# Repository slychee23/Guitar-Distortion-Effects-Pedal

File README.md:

# guitar-distortion-effects-pedal
This is JUJUBE--a custom analog guitar distortion effects pedal using the RC4558 dual op-amp.
<br>
Includes CAD of enclosure with labeled knob controls, optimizing component layouts
<br>
The circuit features:  
<br>
-Three potentiometers for user-adjustable gain, tone, and volume control  
<br>
-A 3PDT footswitch for true bypass switching, with integrated LED indicators for visual feedback  
<br>
-Two 1N4148 silicon diodes configured for symmetrical clipping, creating a distinct, aggressive distortion tone  
<br>

<p align="center">

## Schematic
<p align="center">

## Enclosure
<p align="center">

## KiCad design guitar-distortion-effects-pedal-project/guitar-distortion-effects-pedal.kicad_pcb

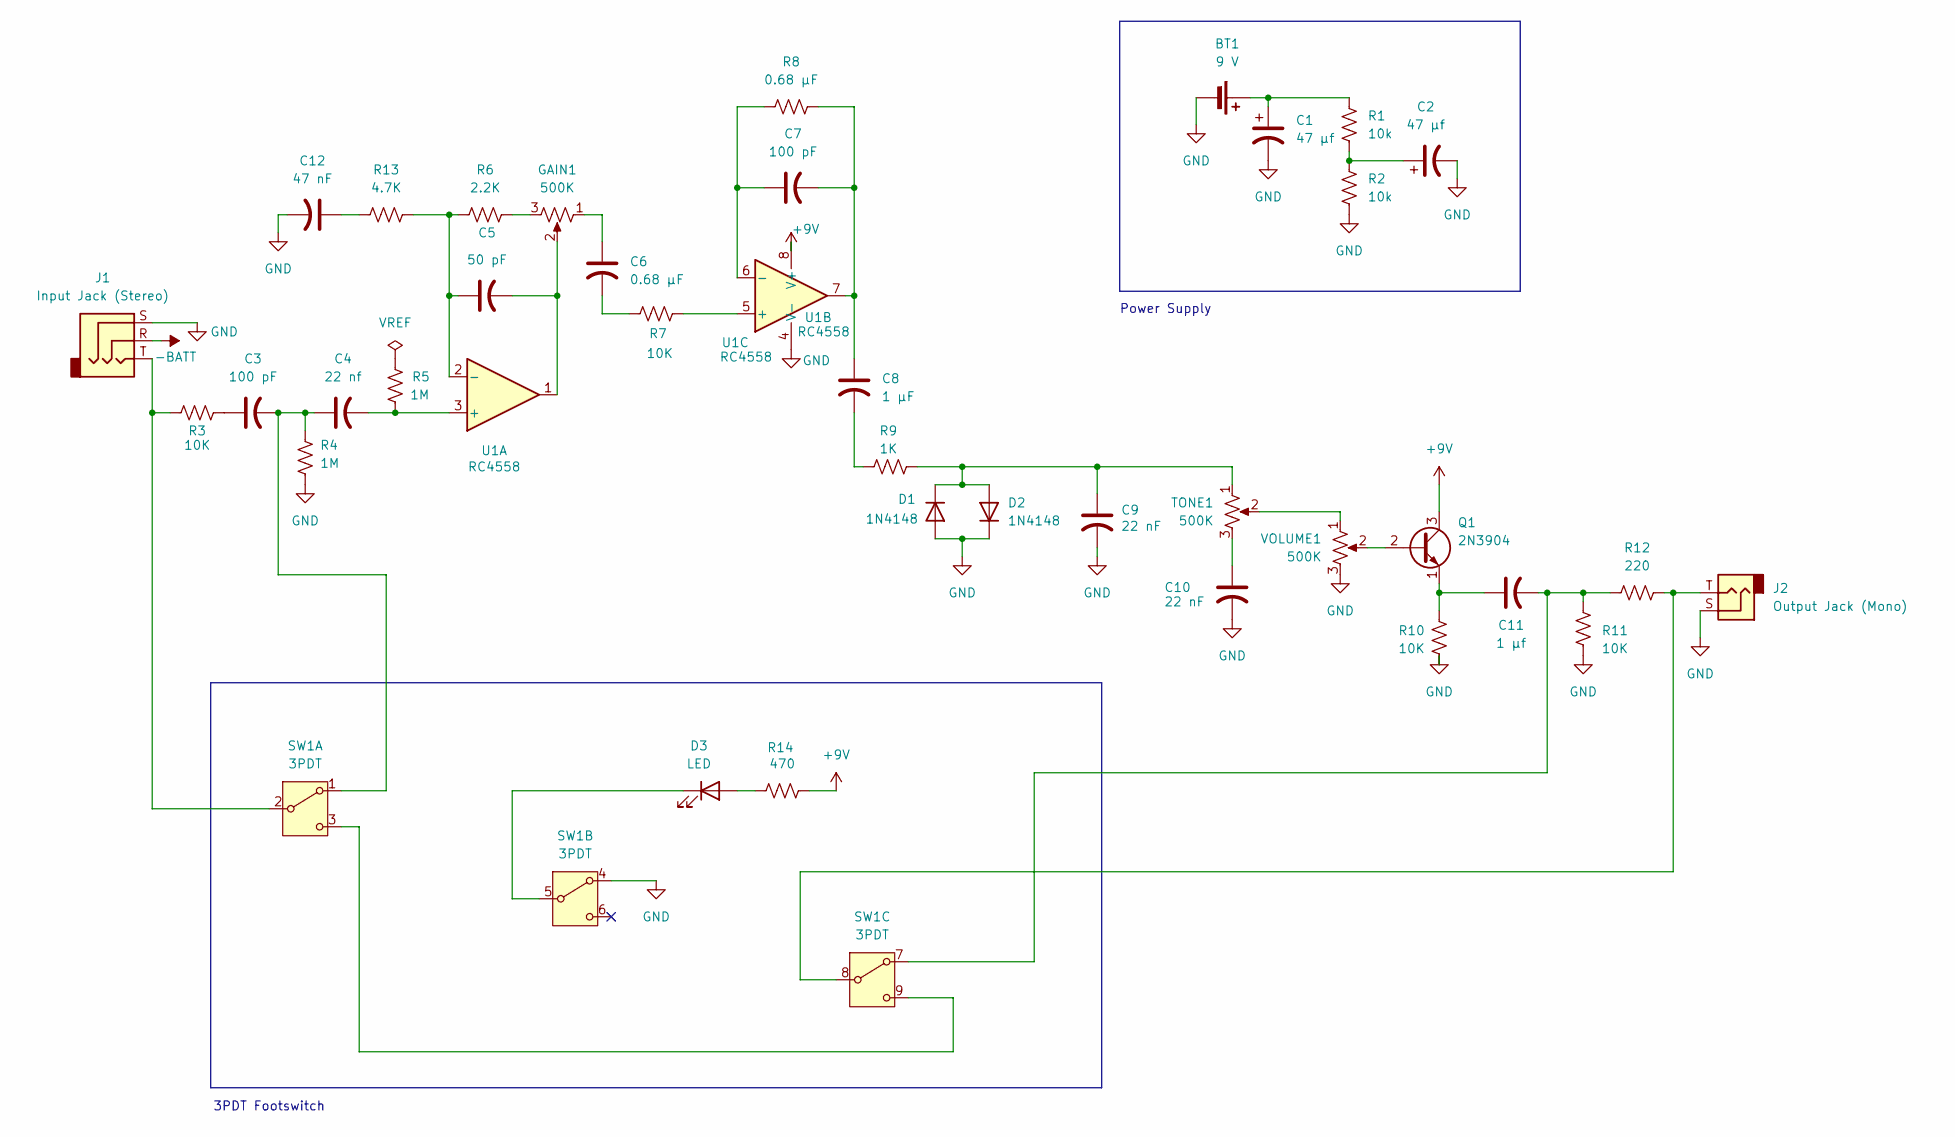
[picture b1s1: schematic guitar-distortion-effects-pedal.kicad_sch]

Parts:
BT1: 9 V; PinSocket_1x02_P2.54mm_Vertical
C1, C2: 47 μf; CP_Radial_D5.0mm_P2.00mm
C3, C7: 100 pF; C_Disc_D4.3mm_W1.9mm_P5.00mm
C4: 22 nf; C_Disc_D4.3mm_W1.9mm_P5.00mm
C5: 50 pF; C_Disc_D4.3mm_W1.9mm_P5.00mm
C6: 0.68 μF; C_Disc_D4.3mm_W1.9mm_P5.00mm
C8: 1 μF; C_Disc_D4.3mm_W1.9mm_P5.00mm
C9, C10: 22 nF; C_Disc_D4.3mm_W1.9mm_P5.00mm
C11: 1 μf; C_Disc_D4.3mm_W1.9mm_P5.00mm
C12: 47 nF; C_Disc_D4.3mm_W1.9mm_P5.00mm
D1, D2: 1N4148; D_DO-41_SOD81_P7.62mm_Horizontal
D3: LED; LED_D5.0mm
GAIN1: 500K; Potentiometer_Bourns_3386W_Horizontal
J1: Input Jack (Stereo); Jack_6.35mm_Neutrik_NJ3FD-V_Vertical
J2: Output Jack (Mono); Jack_6.35mm_Neutrik_NJ2FD-V_Vertical
Q1: 2N3904; TO-92_Inline
R1, R2: 10k; R_Axial_DIN0207_L6.3mm_D2.5mm_P7.62mm_Horizontal
R3, R7, R10, R11: 10K; R_Axial_DIN0207_L6.3mm_D2.5mm_P7.62mm_Horizontal
R4, R5: 1M; R_Axial_DIN0207_L6.3mm_D2.5mm_P7.62mm_Horizontal
R6: 2.2K; R_Axial_DIN0207_L6.3mm_D2.5mm_P7.62mm_Horizontal
R8: 0.68 μF; R_Axial_DIN0207_L6.3mm_D2.5mm_P7.62mm_Horizontal
R9: 1K; R_Axial_DIN0207_L6.3mm_D2.5mm_P7.62mm_Horizontal
R12: 220; R_Axial_DIN0207_L6.3mm_D2.5mm_P7.62mm_Horizontal
R13: 4.7K; R_Axial_DIN0207_L6.3mm_D2.5mm_P7.62mm_Horizontal
R14: 470; R_Axial_DIN0207_L6.3mm_D2.5mm_P7.62mm_Horizontal
SW1: 3PDT; 3PDT_Footswitch
TONE1: 500K; Potentiometer_Bourns_3386W_Horizontal
U1: RC4558; SOIC-8_3.9x4.9mm_P1.27mm
VOLUME1: 500K; Potentiometer_Bourns_3386W_Horizontal

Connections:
+9V: Q1.3 (C), R14.2, U1.8 (V+)
-BATT: J1.R
GND: BT1.2 (-), C1.2, C2.2, C9.2, C10.2, C12.2, D1.2 (A), D2.1 (K), J1.S, J2.S, R2.2, R4.2, R10.2, R11.2, SW1.4 (A), U1.4 (V-), VOLUME1.3
unnamed: BT1.1 (+), C1.1, R1.1
unnamed: C2.1, R1.2, R2.1
unnamed: C3.1, R3.2
unnamed: C5.2, GAIN1.2, U1.1
unnamed: C6.1, GAIN1.1
unnamed: C6.2, R7.1
unnamed: C7.2, C8.1, R8.2, U1.7
unnamed: C8.2, R9.1
unnamed: C10.1, TONE1.3
unnamed: C12.1, R13.1
unnamed: C9.1, D1.1 (K), D2.2 (A), R9.2, TONE1.1
unnamed: D3.2 (A), R14.1
unnamed: D3.1 (K), SW1.5 (B)
unnamed: GAIN1.3, R6.2
unnamed: Q1.2 (B), VOLUME1.2
unnamed: C11.1, Q1.1 (E), R10.1
unnamed: C3.2, C4.1, R4.1, SW1.1 (A)
unnamed: J1.T, R3.1, SW1.2 (B)
unnamed: SW1.3 (C), SW1.9 (C)
unnamed: C11.2, R11.1, R12.1, SW1.7 (A)
unnamed: J2.T, R12.2, SW1.8 (B)
unnamed: TONE1.2, VOLUME1.1
unnamed: C4.2, R5.2, U1.3 (+)
unnamed: C5.1, R6.1, R13.2, U1.2 (-)
unnamed: R7.2, U1.5 (+)
unnamed: C7.1, R8.1, U1.6 (-)

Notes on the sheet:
Power Supply
3PDT Footswitch

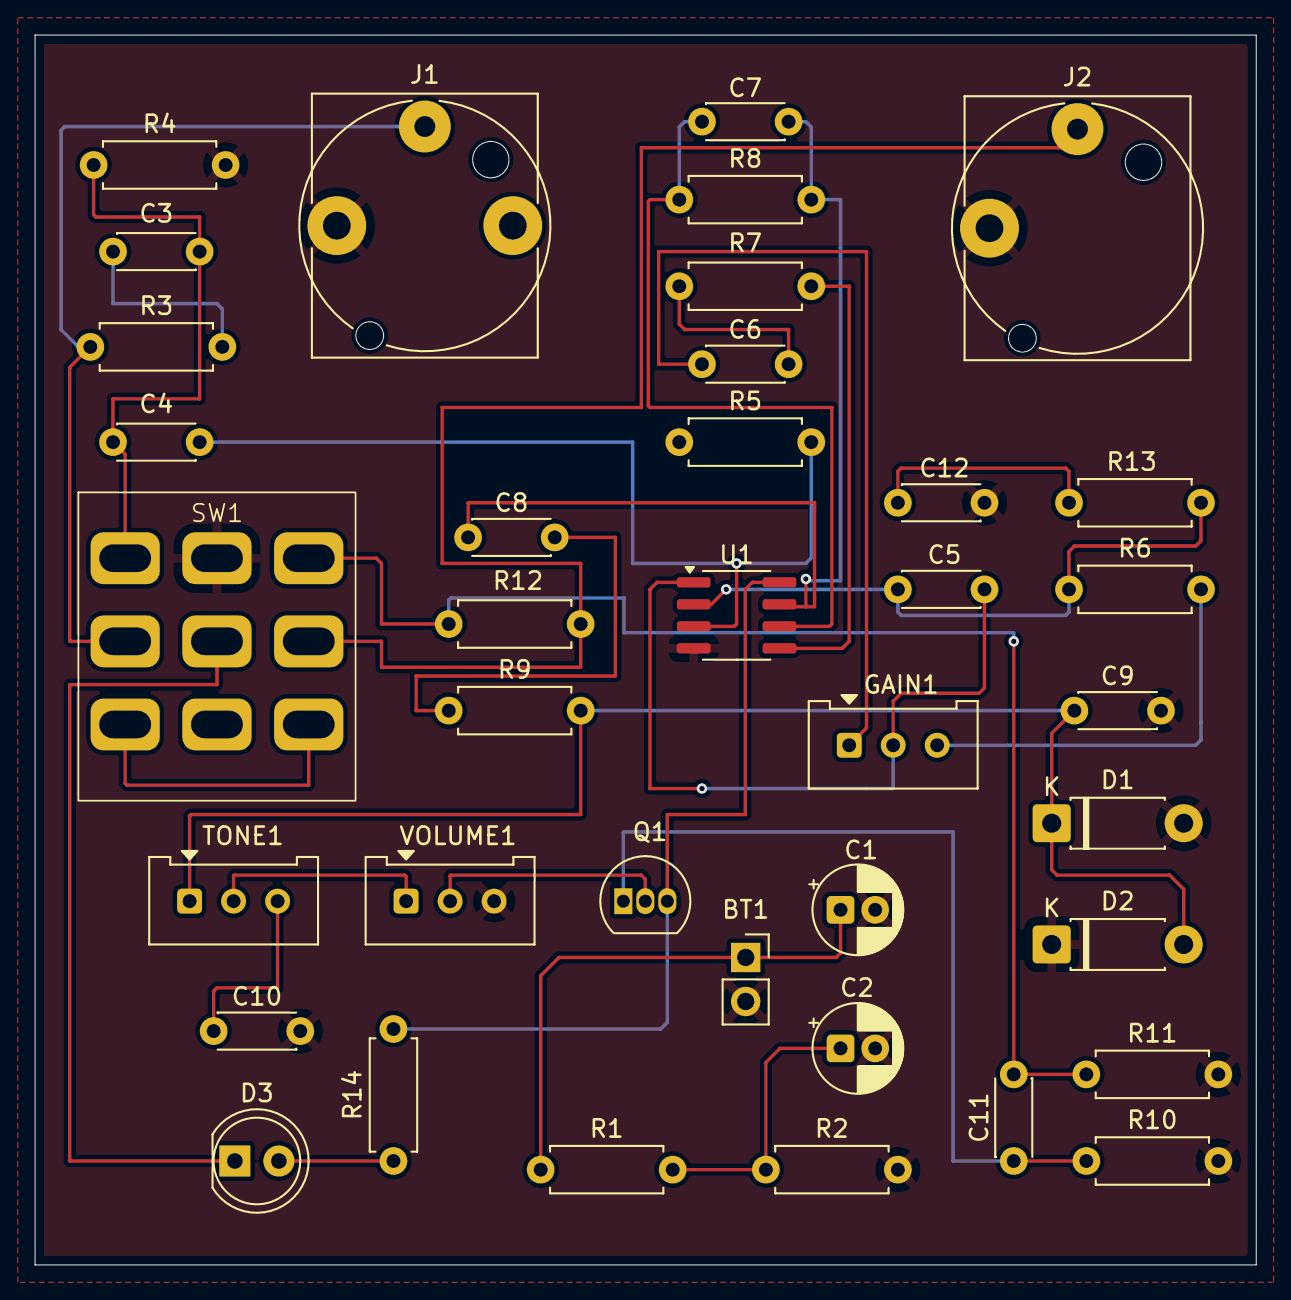
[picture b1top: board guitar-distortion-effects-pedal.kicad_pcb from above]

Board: 2 copper layers, 70.5 x 71.0 mm, 38 parts (0 on the bottom side), 28 nets.
